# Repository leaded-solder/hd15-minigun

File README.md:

This is a version of the [Minigun Supergun](https://www.arcade-projects.com/threads/minigun-supergun-an-open-source-supergun.9408/) open-source supergun that supports HD15 ("VGA") output directly.

## Is it HD15 or VGA?
Technically, the signal being output is not compliant with VGA.

You will need a monitor that supports:
 - 15kHz or 24kHz horizontal sync input (depending on arcade board)
 - Combined sync on the horizontal sync pin

## Monitor compatibility
Tested with:
 - NEC MultiSync 3D CRT

## Version History
### v2
 - Fixed headphone jack with bad footprint
 - Connected HD15 shield to ground
 - Fixed transposed blue and green lines on HD15 connector

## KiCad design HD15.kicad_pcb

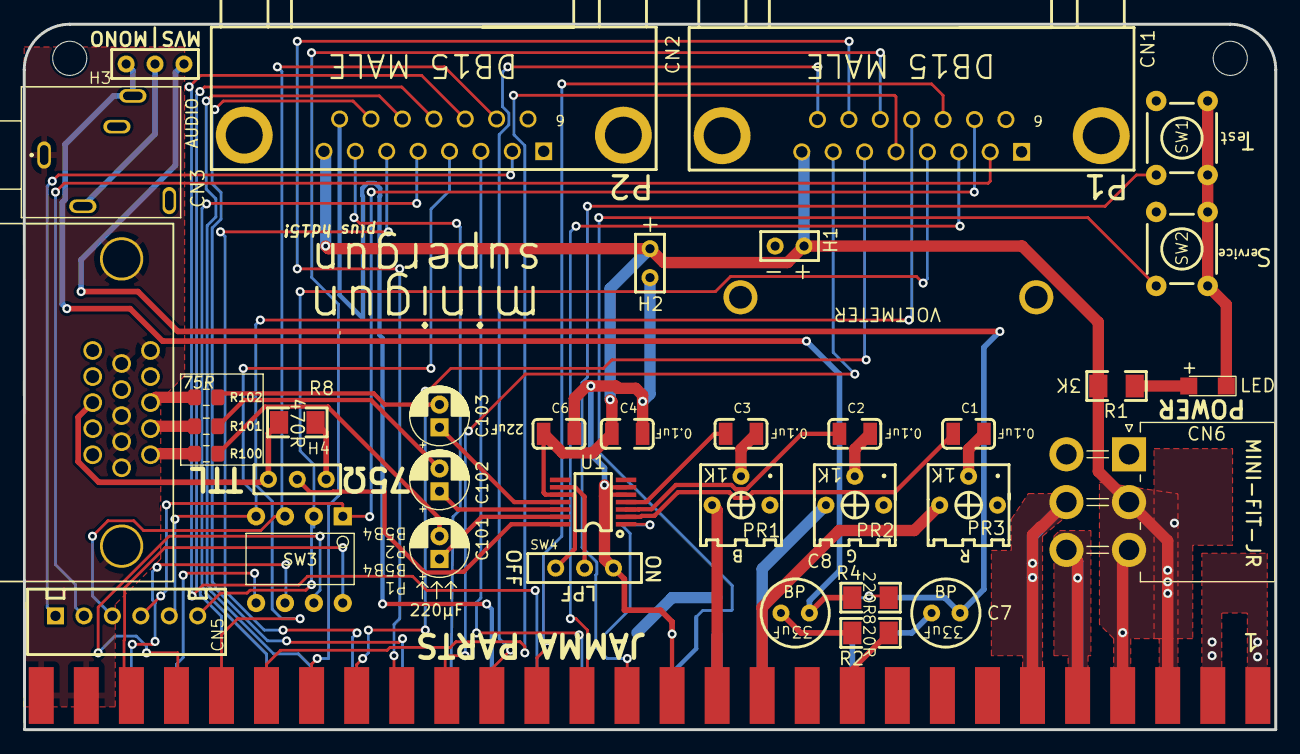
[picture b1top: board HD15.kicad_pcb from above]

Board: 2 copper layers, 110.0 x 62.0 mm, 43 parts (0 on the bottom side), 64 nets.

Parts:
C1, C2, C3, C4, C5, C6: CAPACITOR 1206; CAP_1206
C7, C8: BP; CAPACITOR - TH - 2.5MM PITCH - 6MM ROUND - BP
C101, C102, C103: CP_Radial_D5.0mm_P2.00mm
CN1, CN2: 9; DB15-G-DC
CN3: 35RAPC4BH3; SWITCHCRAFT_35RAPC4BH3
CN5: B6B-XH-A(LF)(SN); JST_XH_6P - B6B-XH-A
CN6: 353180620; MOLEX_MINIFIT-JR-5569-06A2_2X03X4.20MM_ANGLED
H1, H2: HEADER - 2 PIN
H3: HEADER - 3 PIN; 3 PIN HEADER
H4: SYNC; 3 PIN HEADER
J1A, J1B: JAMMA PINS 3.96MM PITCH 2.2MM X 5MM
LED: LED 1206; LED_1206
PR1, PR2, PR3: 3362P-1-102LF; RES-ADJ_3362P
R1, R2, R3, R4, R5, R6, R7, R8: RESISTOR 1206; 1206
R100, R101, R102: R_0805_2012Metric_Pad1.15x1.40mm_HandSolder
SW1, SW2: MJTP1230; TACTILE-PTH
SW3: DIPSwitch-4
SW4: CL-SA-12C-02
U1: THS7374; TSSOP-14
VOLTMETER: VOLTMETER - SEED STUDIO

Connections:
+5V: C4.1, C6.1, CN1.8, CN2.8, CN6.2, CN6.3, H1.2, H2.2, J1A.25, J1A.26, J1B.3, J1B.4, R1.1, SW4.1, U1.10
+12V: CN6.5, J1A.23, J1B.6
-5V: CN6.6, J1A.24, J1B.5
AUDIO: CN3.5, H3.2
GND: C4.2, C6.2, CN1.0, CN1.1, CN2.0, CN2.1, CN3.1, CN6.1, CN6.4, H1.1, H2.1, J1A.1, J1A.2, J1A.15, J1A.27, J1A.28, J1B.1, J1B.2, J1B.27, J1B.28, LED.1, PR1.3, PR2.3, PR3.3, R4.2, R5.2, R7.1, SW1.1, SW1.2, SW2.1, SW2.2, SW4.3, U1.5, U1.6
LED: LED.2, R1.2
LPF: SW4.2, U1.9
P1_B1: CN1.13, J1A.7
P1_B2: CN1.5, J1A.6
P1_B3: CN1.12, J1A.5
P1_B4: CN1.4, CN5.6, SW3.2
P1_B4_J: J1A.4, SW3.7
P1_B5: CN1.10, CN5.4, SW3.1
P1_B5_J: J1A.3, SW3.8
P1_B6: CN1.2, CN5.2
P1_COIN: CN1.3, J1A.13
P1_DOWN: CN1.7, J1A.10
P1_LEFT: CN1.14, J1A.9
P1_RIGHT: CN1.6, J1A.8
P1_START: CN1.11, J1A.12
P1_UP: CN1.15, J1A.11
P2_B1: CN2.13, J1B.22
P2_B2: CN2.5, J1B.23
P2_B3: CN2.12, J1B.24
P2_B4: CN2.4, CN5.5, SW3.4
P2_B4_J: J1B.25, SW3.5
P2_B5: CN2.10, CN5.3, SW3.3
P2_B5_J: J1B.26, SW3.6
P2_B6: CN2.2, CN5.1
P2_COIN: CN2.3, J1B.16
P2_DOWN: CN2.7, J1B.19
P2_LEFT: CN2.14, J1B.20
P2_RIGHT: CN2.6, J1B.21
P2_START: CN2.11, J1B.17
P2_UP: CN2.15, J1B.18
SP+_1: J1A.19, R2.2
SP+_2: C8.1, R2.1
SP+_3: C8.2, CN3.2, H3.1, R4.1
SP-_1: J1B.10, R3.2
SP-_2: C7.1, R3.1
SP-_3: C7.2, H3.3, R5.1
SW_SERVICE: J1B.14, SW2.4
SW_TEST: J1A.14, SW1.4
VIDEO_BLUE: J1A.16, PR1.1
VIDEO_BLUE_1: C3.2, PR1.2
VIDEO_BLUE_2: C3.1, U1.4
VIDEO_BLUE_3: C103.1, U1.11
VIDEO_BLUE_4: C103.2, R102.2
VIDEO_GREEN: J1B.12, PR2.1
VIDEO_GREEN_1: C2.2, PR2.2
VIDEO_GREEN_2: C2.1, U1.3
VIDEO_GREEN_3: C102.1, U1.12
VIDEO_GREEN_4: C102.2, R101.2
VIDEO_RED: J1A.17, PR3.1
VIDEO_RED_1: C1.2, PR3.2
VIDEO_RED_2: C1.1, U1.2
VIDEO_RED_3: C101.1, U1.13
VIDEO_RED_4: C101.2, R100.2
VIDEO_SYNC: J1B.13, R6.2
VIDEO_SYNC_1: C5.2, R6.1, R7.2
VIDEO_SYNC_1A: C5.1, U1.1
VIDEO_SYNC_3: H4.2, U1.14
VIDEO_SYNC_4: H4.3, R8.2
VIDEO_SYNC_5: H4.1, R8.1

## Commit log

2022-03-12 Initial VGA placement, still need to find somewhere for the audio jack
2022-03-12 Full route
2022-03-13 Decoupling caps for R, G, B
2022-03-13 Coupling caps, series resistors for rgb
2022-03-13 Send v0.2 to fab
2022-03-14 Mounting holes down to 2.0mm
2022-03-14 Convert to KiCad 6
2022-03-14 Complete kicad6 conversion
2022-03-28 Fix 5V pour on obverse
2025-01-21 Fix rotated hole in headphone jack
2025-01-21 Fixed headphone jack
2025-01-21 Start tracking fixes
2025-03-21 Fix RBG -> RGB screwup
2025-03-21 Make 75 ohm option obviously preferable
2025-03-21 General label cleanup
2025-03-21 Connect VGA shield to logic ground
2025-03-22 Version notes
2025-03-22 Compat. notes

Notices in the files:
parts and their libraries:
Copyright 2016 Accelerated Designs. All rights reserved.
